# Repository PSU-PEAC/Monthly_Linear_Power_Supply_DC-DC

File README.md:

Monthly_Linear_Power_Supply_DC-DC
=================================

A 30V / 5A Linear DC to DC converter with full Voltage and Current Regulation. MJ4502 PNP output.

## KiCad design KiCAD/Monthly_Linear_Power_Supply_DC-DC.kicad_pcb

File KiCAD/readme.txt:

The KiCAD files
KiCAD build:(2013-07-07 BZR 4022)-stable

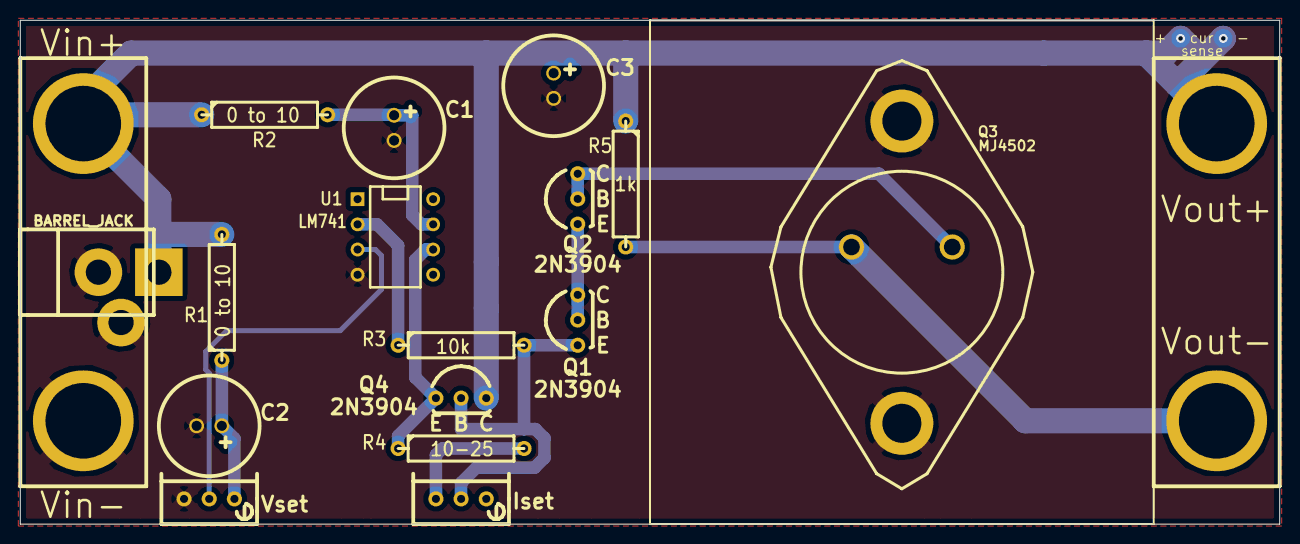
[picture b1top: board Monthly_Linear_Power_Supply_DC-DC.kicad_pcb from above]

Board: 2 copper layers, 127.0 x 50.8 mm, 18 parts (0 on the bottom side), 12 nets.

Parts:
C1, C2, C3: 100uF 50V; Elko_vert_DM10_RM2-5
CON1: BARREL_JACK; JACK_ALIM
Iset: POT; Potentiometer_Bourns_3296W_3-8Zoll_Inline_ScrewUp
P1, P2: CONN_2; 2PIN_6mm
Q1, Q2: 2N3904; TO-92-Bipolar-inline-wide-EBC
Q3: MJ4502; TO3
Q4: 2N3904; TO-92-Inline-EBC
R1, R2: 0 to 10; R5
R3: 10k; R5
R4: 10-25; R5
R5: 1k; R5
U1: LM741; DIP-8__300
Vset: POT; Potentiometer_Bourns_3296W_3-8Zoll_Inline_ScrewUp

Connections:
GND: C1.2, C2.2, C3.2, CON1.2, CON1.3, P2.1, Q3.1, U1.4, Vset.3
unnamed: R3.1, U1.2
unnamed: U1.3, Vset.2
unnamed: Iset.2, Q1.E, Q4.B, R3.2
unnamed: Q4.E, R4.1, U1.6
unnamed: Q1.B, Q1.C, Q2.E
unnamed: C2.1, R1.1, Vset.1
unnamed: Q2.B, Q2.C, Q3.3
unnamed: C1.1, R2.2, U1.7
unnamed: Iset.3, R4.2
unnamed: P1.2, Q3.2, R5.2
VCC: C3.1, CON1.1, P1.1, P2.2, Q4.C, R1.2, R2.1, R5.1
